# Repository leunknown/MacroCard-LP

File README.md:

# MacroCard-LP
A simple credit card sized PCB made for an 8 Key Macropad powered by a Raspberry Pi Pico

## Parts Needed:
- 8x Kailh Low Profile Choc Switches (any Low Profile Choc switch you desire) (From MKUltra)
- 8x Kailh Low Profile Choc Hotswap sockets (From MKUltra)
- 8x Kailh Low Profile Choc Keycaps (regular MX style keycaps would not work) (From MKUltra)
- 1x Raspberry Pi Pico
- 2x 20 male header pins
- 2x 20 female header pins

## Why I chose these parts
- Raspberry Pi Pico is cheap and flexible in terms of what Pin headers and it supports Python, C, and Arduino
- Male and female headers since I don't want to solder the parts directly onto the PCB and make more space for additional keys
- Kailh LP switches since I wanted a low profile macropad.

## Instructions
1. First solder the Kailh hotswap sockets to the back. An easy way to do it is to put solder on one side of the PCB contact, then solder one side and then the other afterwards.

2. Put Male headers (long side) on breadboard and afterwards put the pico on the pins and solder. We do it this way to ensure the header pins are straight.
3. Put the Female header pins onto the pico pins, align it with the back of the PCB (where there is an image of a person and solder the Female headers in place.

4. Solder the rest of the SMD hotswap sockets by first tinning one pad, then placing the socket and heat up the part touching the tinned pad. Afterwards, solder the other pad. Repeat this process until all sockets are soldered on.
5. To code the Pico, pick a programming language to use and code!

## Final Product

## MISC
- I like getting parts from MKUltra as their parts are cheaper and relatively more resonable than other vendors. (unless you want to wait for a month from AliExpress)

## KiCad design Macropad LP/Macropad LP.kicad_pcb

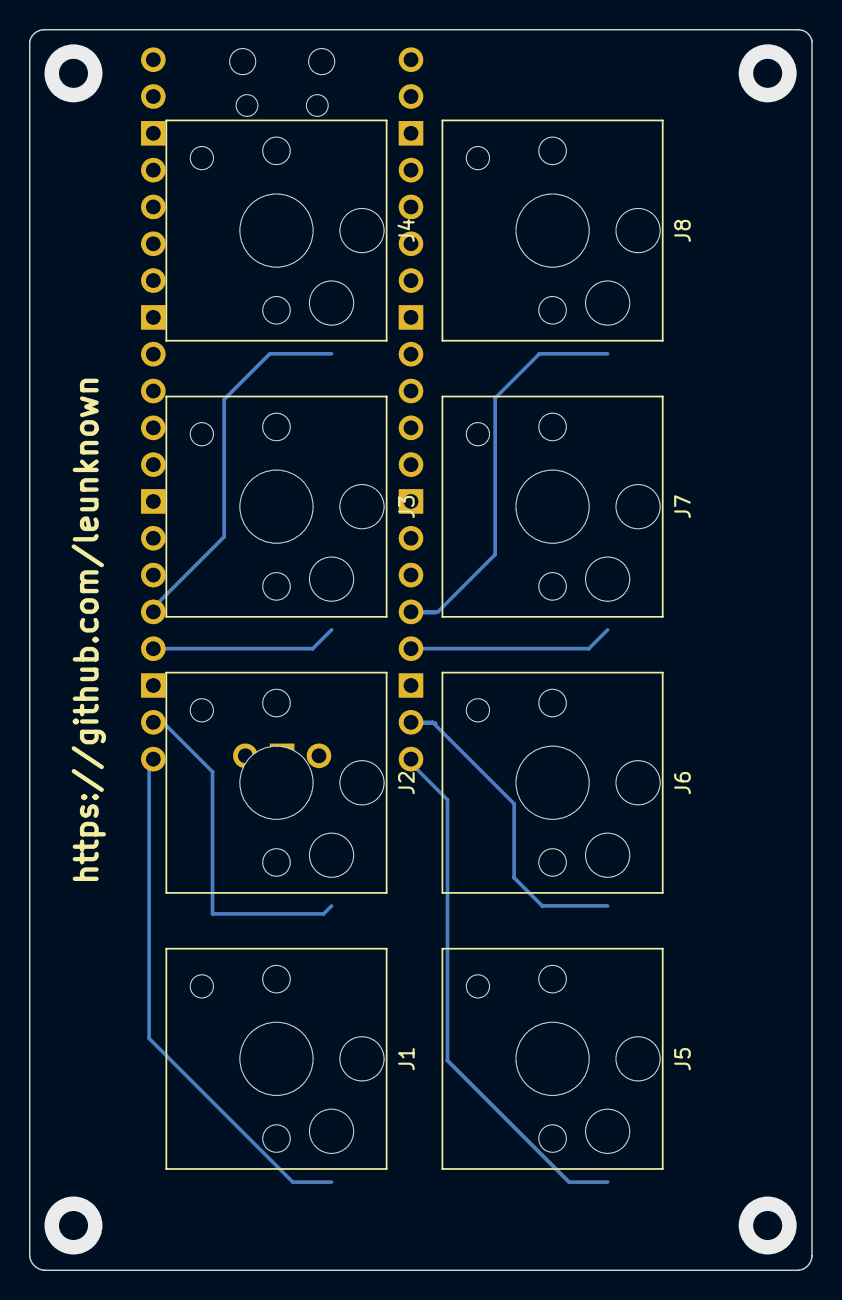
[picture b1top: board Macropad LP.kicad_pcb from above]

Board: 2 copper layers, 54.0 x 85.6 mm, 9 parts (1 on the bottom side), 9 nets.

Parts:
J1: switch 1; SW_Hotswap_Kailh_Choc_V1V2
J2: switch 2; SW_Hotswap_Kailh_Choc_V1V2
J3: switch 3; SW_Hotswap_Kailh_Choc_V1V2
J4: switch 4; SW_Hotswap_Kailh_Choc_V1V2
J5: switch 5; SW_Hotswap_Kailh_Choc_V1V2
J6: switch 6; SW_Hotswap_Kailh_Choc_V1V2
J7: switch 7; SW_Hotswap_Kailh_Choc_V1V2
J8: switch 8; SW_Hotswap_Kailh_Choc_V1V2
U1: Pico; RPi_Pico_SMD_TH

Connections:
unnamed: J1.2, U1.21 (GPIO16)
unnamed: J2.2, U1.22 (GPIO17)
unnamed: J3.2, U1.24 (GPIO18)
unnamed: J4.2, U1.25 (GPIO19)
unnamed: J5.2, U1.20 (GPIO15)
unnamed: J6.2, U1.19 (GPIO14)
unnamed: J7.2, U1.17 (GPIO13)
unnamed: J8.2, U1.16 (GPIO12)
Out: J1.1, J2.1, J3.1, J4.1, J5.1, J6.1, J7.1, J8.1, U1.36 (3V3)

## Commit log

2022-04-26 Update README.md
    first revision
2022-04-26 Gerber File Zip for PCB
2022-04-26 KiCad 6.0 File for PCB
2022-06-01 3D Print File for Case and SolidWorks file
    I got lazy, the case is a bit too tall in my opinion, feel free to change it.

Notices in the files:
Macropad LP/Macropad LP.kicad_pcb:
©2022
